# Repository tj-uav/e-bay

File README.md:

# e-bay
Electronics bay PCB for avalon

See Avalon X -> Improvements -> Ebay for the full MCAD assembly.

Designed to take 3-4S battery input through an XT60 connector and power a Pixhawk 2.4.8, Raspberry Pi 4, 5.5V Servo rail, Bullet AC, camera gimbal, plus one extra XT60 connector. Requires three buck converter modules (The servo rail buck must be rated for 5A, the other two may be between 3A and 5A). The Raspberry Pi buck module should be set to 5V flat. The Pixhawk buck module should be set to around 5.3V. The servo rail buck module should be set to 5-5.5V. Use a wire to connect the two PCBs, with the left side PCB receiving power from the battery and the right side PCB receiving power from the left. Because of a CAD mistake, the wire needs to be soldered to the right side PCB, while the left side can support an XT60 connector. Use 16AWG or thicker wire to handle high ish currents.

Molex cables going to the Pixhawk should have the same pinout on both ends of the cable (i.e. pin 1 is power). This is opposite of pixhawk convention, which mirrors the connector pinout on either end. Do NOT use pixhawk cables on this PCB.

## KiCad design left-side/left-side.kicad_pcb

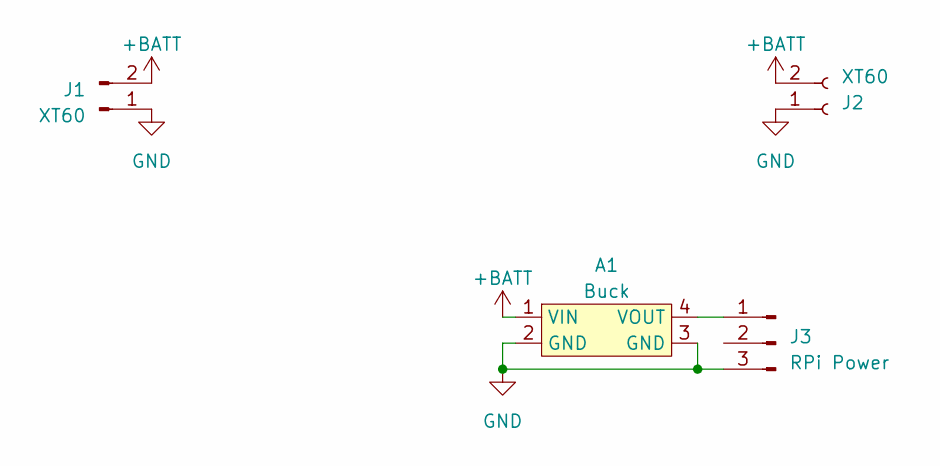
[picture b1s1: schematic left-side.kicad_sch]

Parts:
A1: Buck
J1: XT60; AMASS_XT60-M_1x02_P7.20mm_Vertical
J2: XT60; AMASS_XT60-F_1x02_P7.20mm_Vertical
J3: RPi Power; PinHeader_1x03_P2.54mm_Vertical

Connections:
+BATT: A1.1 (VIN), J1.2, J2.2
GND: A1.2 (GND), A1.3 (GND), J1.1, J2.1, J3.3
unnamed: A1.4 (VOUT), J3.1

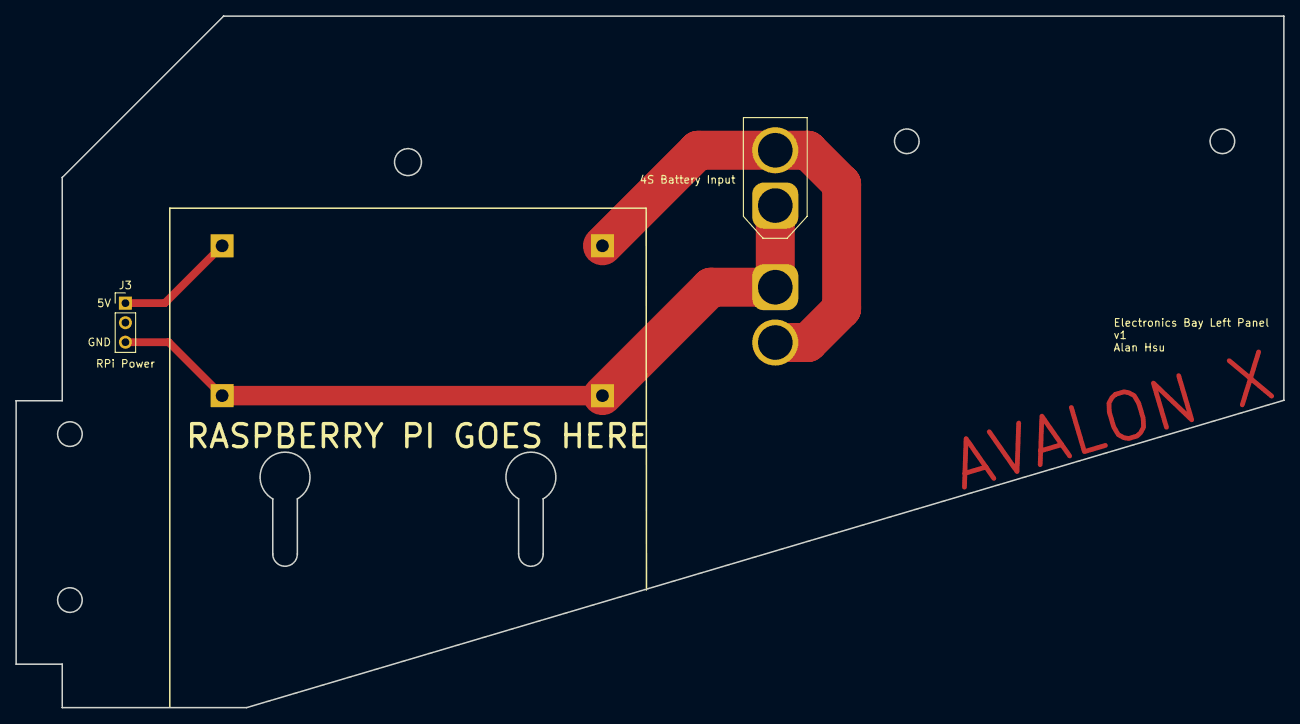
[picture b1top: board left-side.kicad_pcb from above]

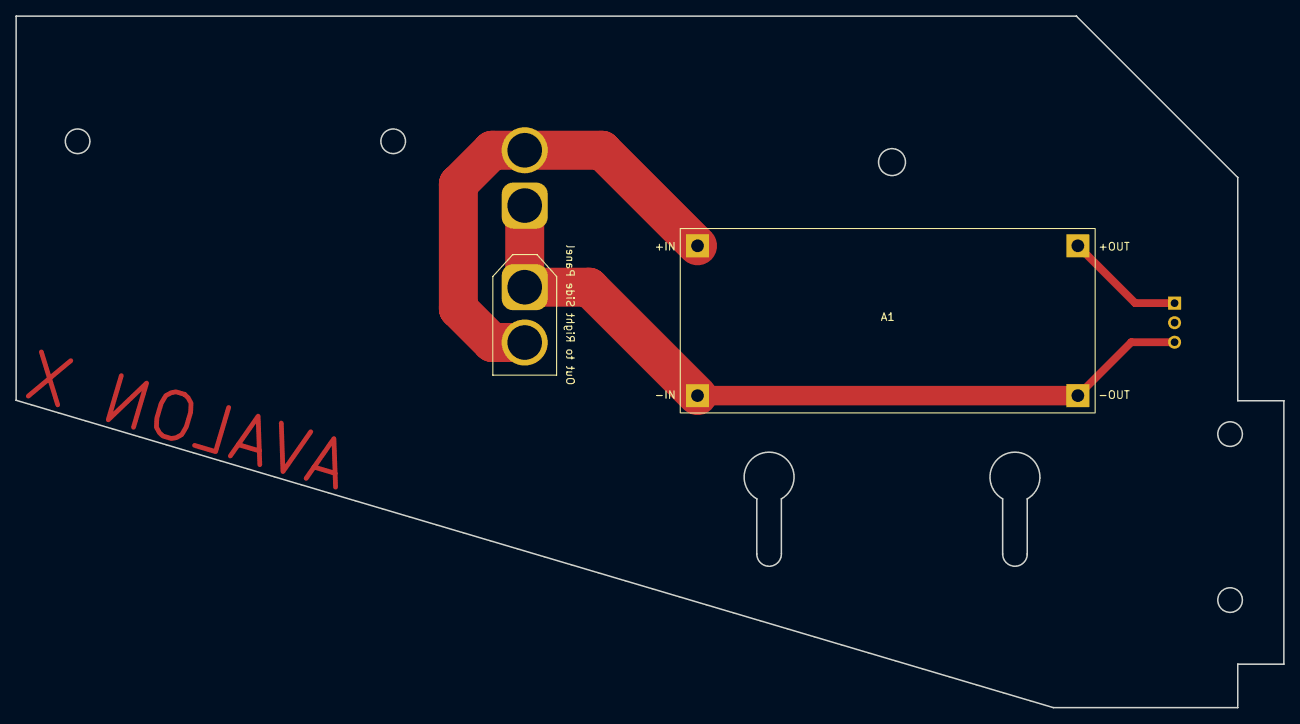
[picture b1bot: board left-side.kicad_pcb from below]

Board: 2 copper layers, 165.0 x 90.0 mm, 4 parts (2 on the bottom side), 3 nets.

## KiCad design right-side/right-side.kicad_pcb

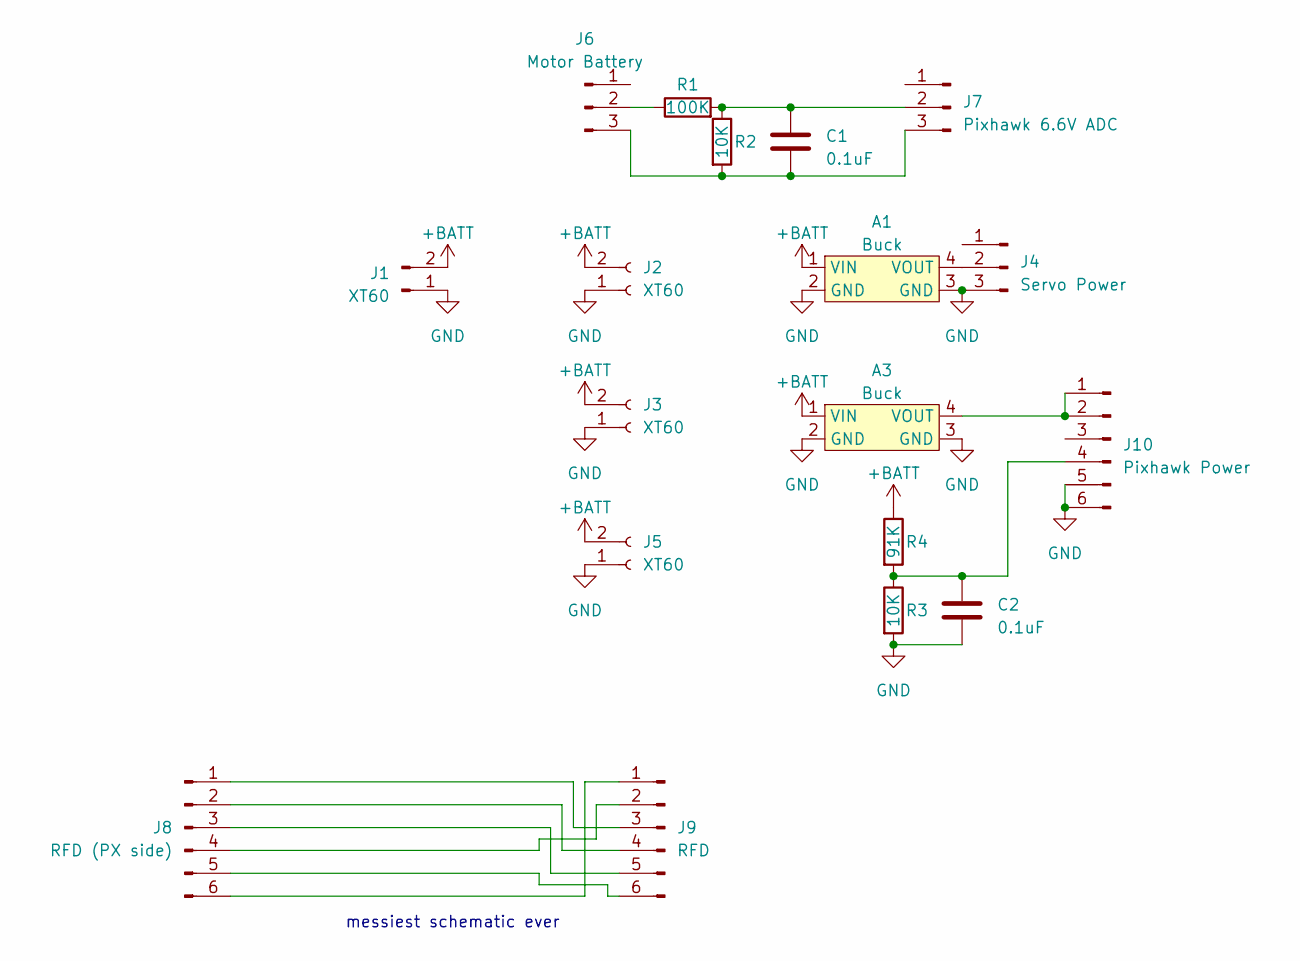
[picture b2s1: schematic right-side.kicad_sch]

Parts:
A1, A3: Buck
C1, C2: 0.1uF; C_Disc_D5.0mm_W2.5mm_P5.00mm
J1: XT60; AMASS_XT60-M_1x02_P7.20mm_Vertical
J2, J3, J5: XT60; AMASS_XT60-F_1x02_P7.20mm_Vertical
J4: Servo Power; PinHeader_1x03_P2.54mm_Vertical
J6: Motor Battery; PinHeader_1x03_P2.54mm_Vertical
J7: Pixhawk 6.6V ADC; Hirose_DF13-03P-1.25DSA_1x03_P1.25mm_Vertical
J8: RFD (PX side); Hirose_DF13-06P-1.25DSA_1x06_P1.25mm_Vertical
J9: RFD; PinHeader_1x06_P2.54mm_Vertical
J10: Pixhawk Power; Hirose_DF13-06P-1.25DSA_1x06_P1.25mm_Vertical
R1: 100K; R_Axial_DIN0207_L6.3mm_D2.5mm_P10.16mm_Horizontal
R2, R3: 10K; R_Axial_DIN0207_L6.3mm_D2.5mm_P10.16mm_Horizontal
R4: 91K; R_Axial_DIN0207_L6.3mm_D2.5mm_P10.16mm_Horizontal

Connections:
+BATT: A1.1 (VIN), A3.1 (VIN), J1.2, J2.2, J3.2, J5.2, R4.1
GND: A1.2 (GND), A1.3 (GND), A3.2 (GND), A3.3 (GND), C2.2, J1.1, J2.1, J3.1, J4.3, J5.1, J10.5, J10.6, R3.2
unnamed: A1.4 (VOUT), J4.2
unnamed: A3.4 (VOUT), J10.1, J10.2
unnamed: J6.2, R1.1
unnamed: C1.2, J6.3, J7.3, R2.2
unnamed: C1.1, J7.2, R1.2, R2.1
unnamed: J8.1, J9.3
unnamed: J8.2, J9.4
unnamed: J8.3, J9.5
unnamed: J8.4, J9.2
unnamed: J8.5, J9.6
unnamed: J8.6, J9.1
unnamed: C2.1, J10.4, R3.1, R4.2

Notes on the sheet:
messiest schematic ever

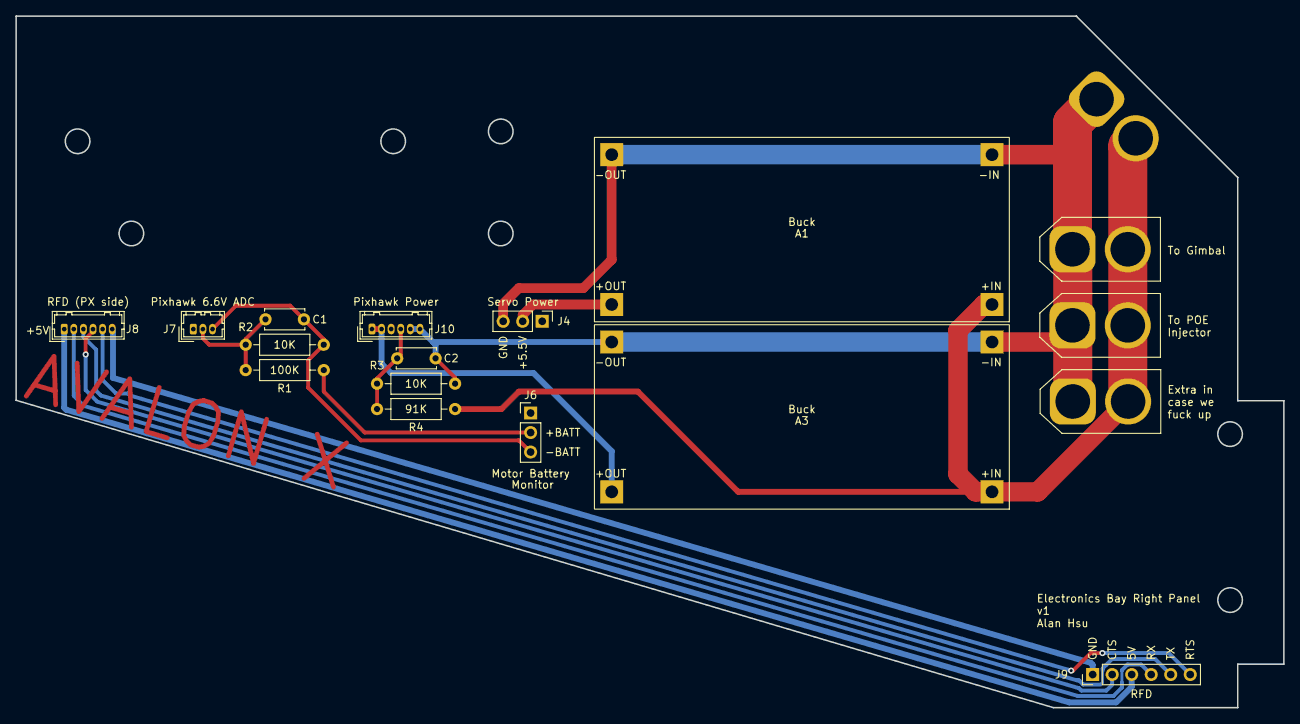
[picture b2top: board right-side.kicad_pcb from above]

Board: 2 copper layers, 165.0 x 90.0 mm, 18 parts (1 on the bottom side), 14 nets.

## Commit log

2023-03-03 first work
2023-03-03 update outlines, finish left side
2023-03-08 finalize both panels
2023-03-08 gitignore update
2023-03-08 gerber export
2023-03-08 gerber zips and step exports
